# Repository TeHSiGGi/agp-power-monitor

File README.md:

# AGP Power Monitor

The APM is a monitoring tool to determine the exact power consumption of an AGP Graphics Card.
It measures both power provided by the AGP slot as well as through external power sources via: 

- 6 pin Mini-Fit Jr. from Molex (PCIe Power) 
- 4 Pin AMP Mate-n-Lok 1-480424-0 (mostly known as Molex connector, though it isn't one).

## Hardware

At the heart of APM is a custom AGP Riser card which consists mainly of an STM32F103C8T6 and three INA3221 power monitors. 

It measures the voltages and currents of the AGP slot as well as of external power providers. Additionally there are two alternative inputs which can be used to measure any user-chosen external power rail as long as it is within specification.

### Power Rails

The following power rails are being measured by the APM.

| Interface | Rail |
| -- | -- |
| AGP slot | 12V |
| AGP slot | 5V |
| AGP slot | 3.3V |
| AGP slot | VDDQ |
| External power | 12V (6Pin) |
| External power | 12V (4Pin) |
| External power | 5V (4Pin) |
| Alternative input | A |
| Alternative input | B |

### Resolution and limits

Each rail can measure:

- Up to 26V of voltage at 8mV steps
- Up to 10A of current at 4mA steps

These resolution values have to be take with a grain of salt, since these are theoretical numbers. The 26V and 10A are the absolute maximum ratings and must not be exceeded at any time.

### Connections:

- 2 keyed AGP gold finger connector
- Universal AGP slot
- Mini-Fit Jr 6 Pin input and output
- Mate-n-Lok 4 Pin input and output
- 2 Screw terminals for alternative channels A and B
- 4 Pin header for additional I2C devices
- 4 Pin header for STlink programming
- USB Mini B interface for connecting to a PC running the monitoring software

## Firmware

The APM uses an STM32F103C8T6 as its main processor. It serves as a USB interface providing fast access to the data provided by the INA3221.

The firmware is built using Platform.io and programmed via the 4 pin header on the board using STlink.

## Software

The monitoring software for APM is written in python and provides the following capabilities:

- Real time monitoring of all power rails (voltage, current, power)
- Automated calculation of minimum, maximum and average values over time of measurement
- Automated calculation of overall power per interface (AGP slot, external power and alternative inputs)
- Automated calculation of total power of all interfaces combined

## Known issues

- The layout of the AGP gold-fingers is a bit offset in the second and third segment
- CRC checking in the python application not implemented

## Wishlist for the future

- Plotting

## Reference values

To see some values from measured graphics cards, see [reference values](https://tehsiggi.github.io/agp-power-monitor/)

## Disclaimer

This project is provided as is. There is no support or warranty on any parts of it (this includes hardware design, firmware and software). Use it at your own risk.

The author will not be accountable for any damage or harm inflicted.

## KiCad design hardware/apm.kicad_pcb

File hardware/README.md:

# AGP Power Monitor Hardware

## Project Overview

The AGP Power Monitor is uses a custom AGP riser card to measure and monitor power consumption of AGP cards. It provides real-time voltage and current measurements for the various power rails used by AGP graphics cards, allowing for detailed power analysis and troubleshooting.

## Hardware Design

### Main Components

- **AGP Connectors**: Edge connector for AGP cards and slot connector for motherboard interface
- **Power Measurement**: INA3221 triple-channel power monitors for measuring voltage and current
- **Microcontroller**: STM32F103C8T6 MCU for data processing and USB communication
- **Power Supply**: All logic is powered via the USB input
- **USB Interface**: USB connectivity for data output and device control

### Design Notes

The PCB is a multi-layer design featuring:
- 4 layer with dedicated ground and power planes
- length matches AGP data lines

The USB input is using a polyfuse to prevent damage in case of shortcuts. The 3.3V output of the onboard regulator must not be loaded with more than 250mA. 

You can use the I2C header to connect additional hardware if needed.

The board features pin headers on the backside that can be used for calibration and rail measurement with external measurement equipment.

### Key Features

1. **Inline Power Measurement**: Non-intrusive monitoring between motherboard and graphics card
2. **Multiple Rail Monitoring**: Simultaneous monitoring of AGP power rails (3.3V, 5V, 12V, VDDQ)
3. **External Power Input**: Additional power connectors for supplementary power testing
4. **I²C Expansion**: I²C interface for connecting additional sensors or displays
5. **USB Interface**: Data logging and real-time monitoring via USB

## Connectors and Interfaces

| Connector | Description | Function |
|-----------|-------------|----------|
| J201 | AGP Edge Connector | Connects to motherboard AGP slot |
| J202 | AGP Slot Connector | Receives AGP graphics card |
| J301/J302 | External Power | 6Pin External 12V power input connectors |
| J303/J304 | External Power | 4Pin 5V/12V power output connector |
| J305/J306 | Alternative Power | Alternative power measurement points |
| J501 | USB Connector | USB data interface |
| J502 | I²C Header | External I²C device connection |

## KiCad Files and Libraries

This project is designed using KiCad 9.0. The directory includes:

- `apm.kicad_pro` - KiCad project file
- `apm.kicad_sch` - Main schematic file
- `apm.kicad_pcb` - PCB layout file
- `lib/` - Custom component libraries:
  - AGP edge connector footprints and symbols
  - AGP slot connector footprints and symbols
  - Power connector footprints and symbols

### Schematic Organization

The schematic is organized into multiple sheets for clarity:

1. **Main Sheet**: Overall system connections
2. **AGP Connectors**: AGP interface connections
3. **External Power**: Power input and conditioning circuits
4. **Sensors**: Power measurement circuits using INA3221
5. **USB Interface**: STM32 microcontroller and USB interface

## Setup Instructions

### Assembly Notes

1. The board requires SMD soldering capabilities (down to 0603 components, QFN packages)
2. Pay special attention to the alignment of AGP connectors
3. The PCB is designed for standard 1.6mm thickness
4. Edge plating is required for the AGP edge connector
5. Beveling (20°) is used during manufacturing

The PCBs have successfully been manufactured at pcbway.com

## BOM

| Part Type | Value/Model | Footprint | Qty | Comment |
|-----------|-------------|-----------|-----|---------|
| Capacitors | 4µ7 | 1206 | 2 | Bulk capacitors for 12V rail |
| | 22µ | 1206 | 12 | Bulk capacitors for 3.3V, 5V and VDDQ rail, USB Bus power |
| | 1µ | 0603 | 10 | Bypass capacitors for external and alternative inputs |
| | 100n | 0603 | 16 | Bypass capacitors and filter capacitors for INA3221|
| | 10µ | 1206 | 1 | Bypass capacitor for 3.3V from USB power |
| | 20p | 0603 | 4 | Crystal load capacitors |
| | 10n | 0603 | 1 | Capacitor for reset circuit |
| Resistors | 0R01 | 2816 | 9 | Current shunt resistors |
| | 10 | 0603 | 18 | Pull-up/pull-down resistors |
| | 22 | 0603 | 2 | USB termination resistors |
| | 1M | 0603 | 1 | Crystal load resistor |
| | 10k | 0603 | 1 | Pull-up resistor |
| | 4k7 | 0603 | 1 | Pull-up resistor |
| | 3k3 | 0603 | 3 | Pull-up resistors |
| | 220 | 0603 | 3 | LED current limiting resistors |
| ICs | INA3221 | VQFN | 3 | Triple-channel power monitor |
| | MCP1703AT3302ECB | SOT-23 | 1 | 3.3V voltage regulator |
| | STM32F103C8T6 | LQFP-48 | 1 | 32-bit ARM microcontroller |
| Protection | PRTR5V0U2X | SOT-143 | 2 | USB ESD protection |
| | P4SMAJ5.0A | SMA | 1 | TVS diode |
| | 200mA | 1812 | 1 | Polyfuse |
| Connectors | AGP Edge Connector | edge_universal | 1 | Motherboard interface |
| | 145376-2 | 145376-2 AMP | 1 | AGP card slot |
| | 12V/3.3V/VDDQ/5V/GND PROBE | Pin Header 2 Pin 2.54mm | 10 | Test points |
| | 39301060 | Molex_Mini-Fit_Jr_5569-06A2_2x03_P4.20mm_Horizontal | 2 | 6-pin power connectors |
| | 641737-1 | 641737-1 | 2 | 4-pin power connectors |
| | Screw_Terminal_01x02 | 5.08mm Horizontal | 2 | Alternative power input |
| | USB_B_Mini | Wuerth 65100516121 | 1 | USB interface |
| | I2C/STLink Headers | PinHeader 4 Pin 2.54mm | 2 | Expansion/Programming headers |
| Indicators | LED | 1206 | 3 | Status indicators |
| Crystals | 8MHz | HC49l | 1 | Main MCU oscillator |
| | 32.768kHz | DS10 | 1 | RTC oscillator |

## Revision History

- Rev 1.0.0: Initial hardware design

## Disclaimer

This project is provided as is. There is no support or warranty on any parts of it (this includes hardware design, firmware and software). Use it at your own risk.

The author will not be accountable for any damage or harm inflicted.

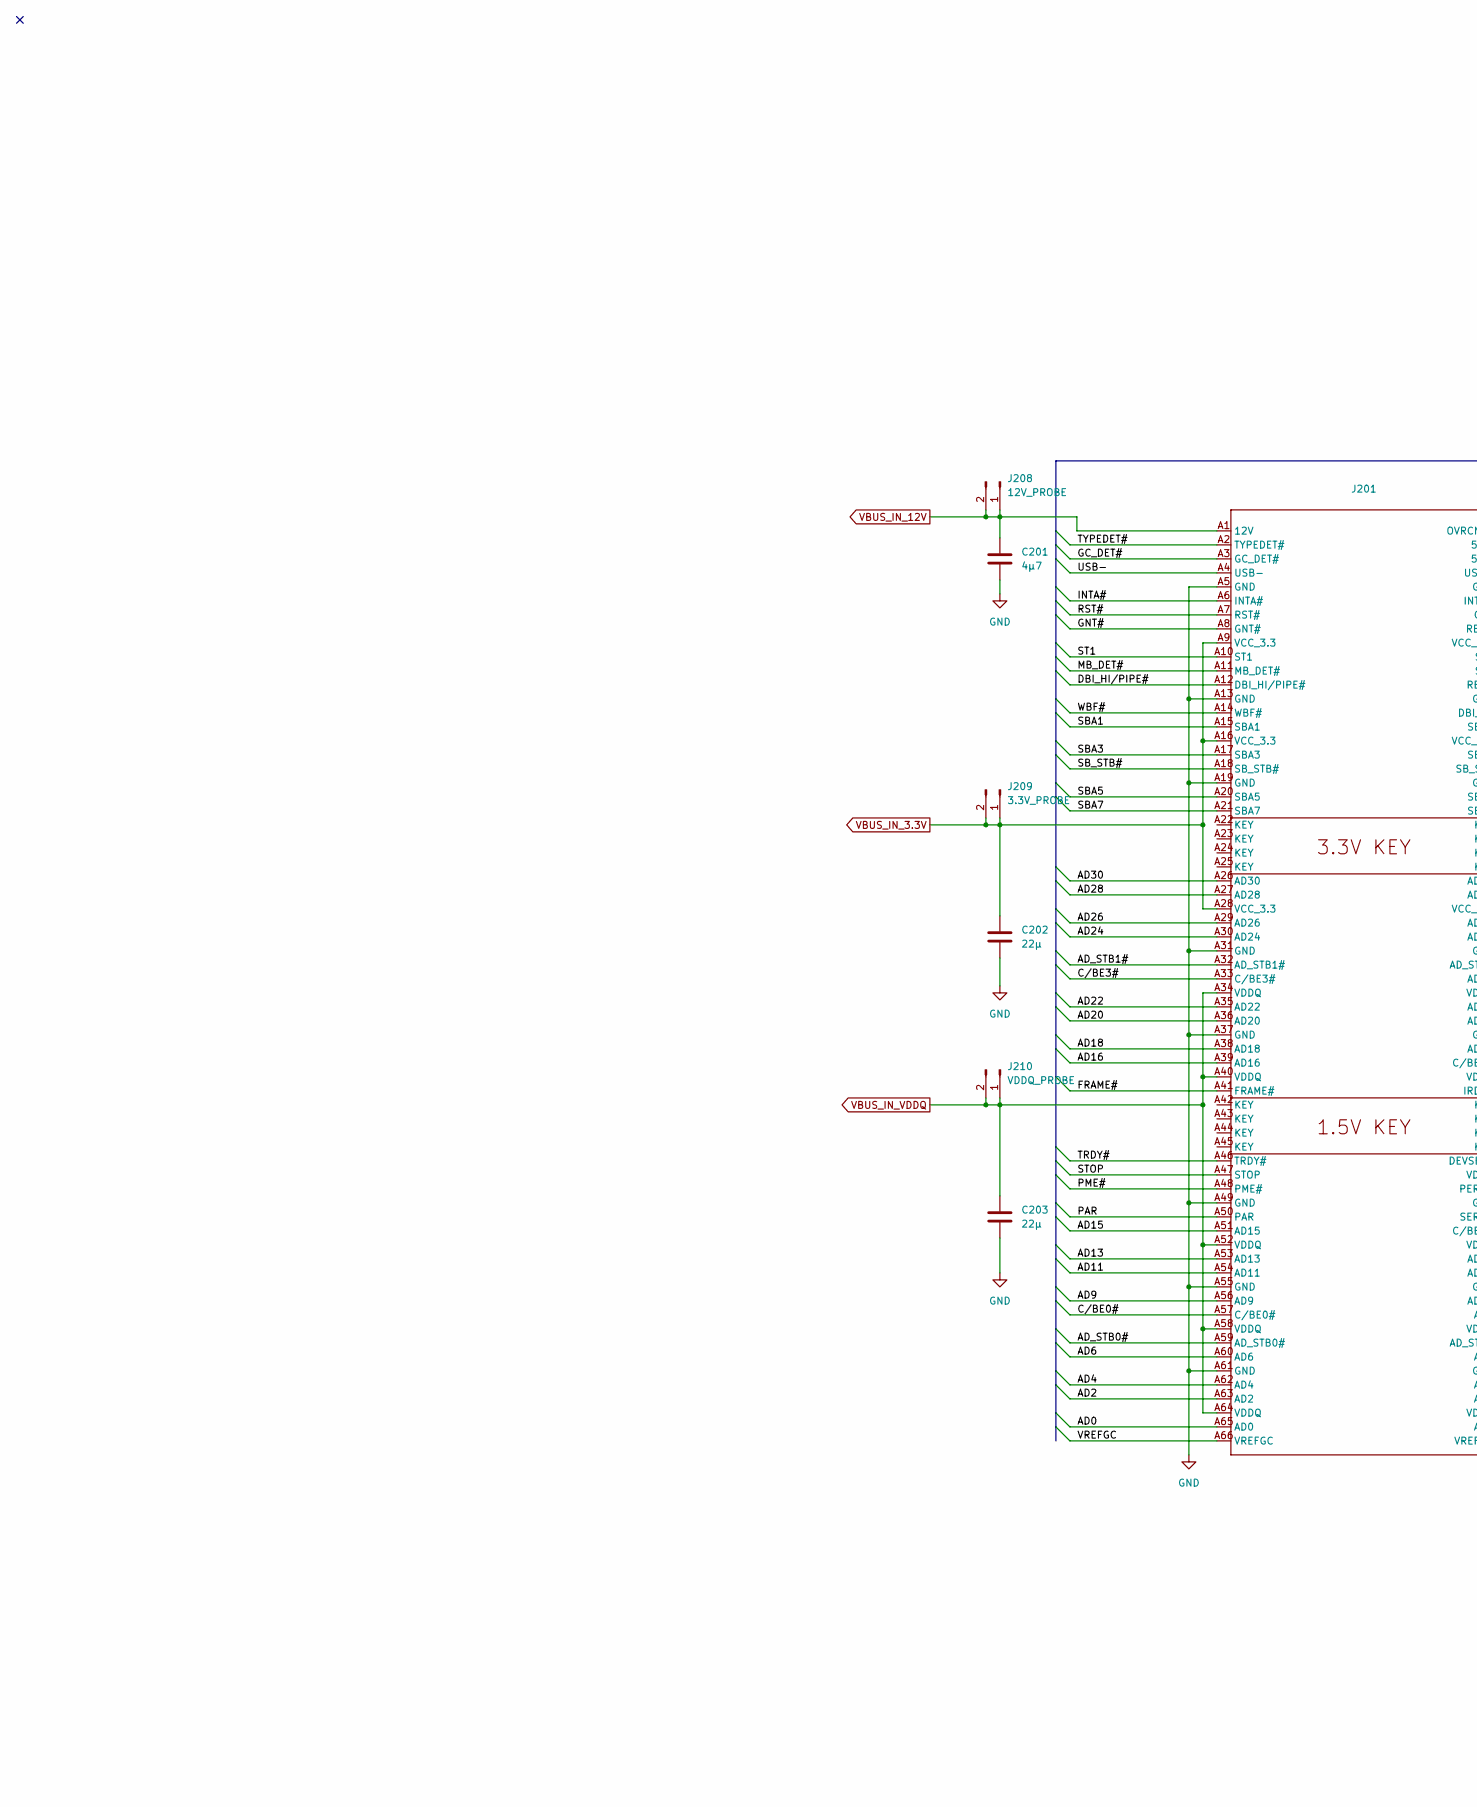
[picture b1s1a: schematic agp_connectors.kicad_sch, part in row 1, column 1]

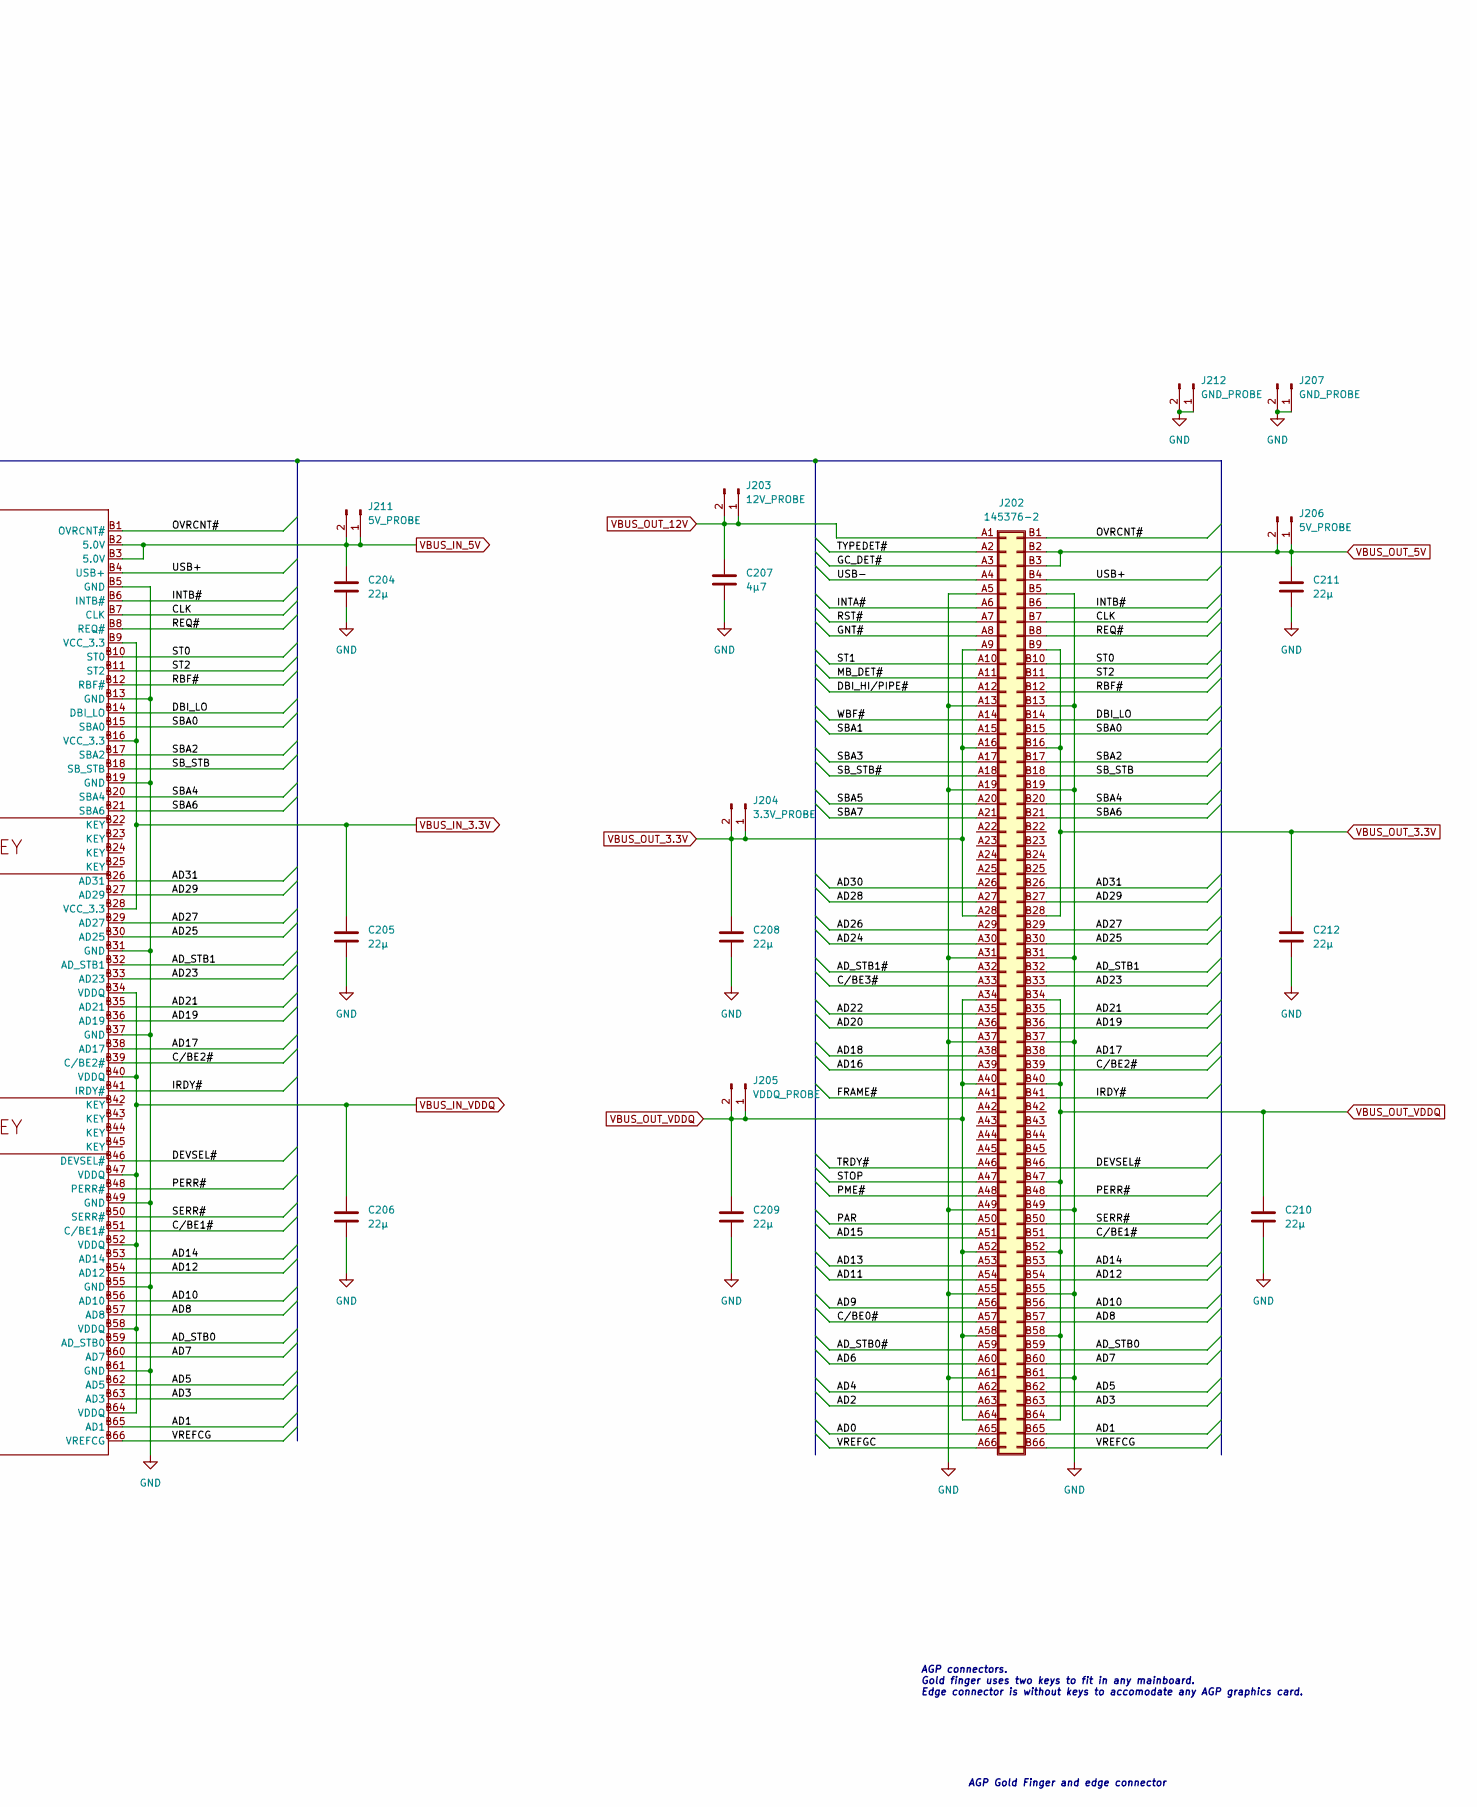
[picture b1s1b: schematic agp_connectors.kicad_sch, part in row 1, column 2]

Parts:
C201, C207: 4µ7; C_1206_3216Metric
C202, C203, C204, C205, C206, C208, C209, C210, C211, C212: 22µ; C_1206_3216Metric
J201: edge_universal
J202: 145376-2; Conn_AMP_1MM_STD_EDGE_132_POS_145376-2
J203, J208: 12V_PROBE; PinHeader_1x02_P2.54mm_Vertical
J204, J209: 3.3V_PROBE; PinHeader_1x02_P2.54mm_Vertical
J205, J210: VDDQ_PROBE; PinHeader_1x02_P2.54mm_Vertical
J206, J211: 5V_PROBE; PinHeader_1x02_P2.54mm_Vertical
J207, J212: GND_PROBE; PinHeader_1x02_P2.54mm_Vertical

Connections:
/agp_connectors/AD0: J201.A65 (AD0), J202.A65 (65)
/agp_connectors/AD1: J201.B65 (AD1), J202.B65 (131)
/agp_connectors/AD2: J201.A63 (AD2), J202.A63 (63)
/agp_connectors/AD3: J201.B63 (AD3), J202.B63 (129)
/agp_connectors/AD4: J201.A62 (AD4), J202.A62 (62)
/agp_connectors/AD5: J201.B62 (AD5), J202.B62 (128)
/agp_connectors/AD6: J201.A60 (AD6), J202.A60 (60)
/agp_connectors/AD7: J201.B60 (AD7), J202.B60 (126)
/agp_connectors/AD8: J201.B57 (AD8), J202.B57 (123)
/agp_connectors/AD9: J201.A56 (AD9), J202.A56 (56)
/agp_connectors/AD10: J201.B56 (AD10), J202.B56 (122)
/agp_connectors/AD11: J201.A54 (AD11), J202.A54 (54)
/agp_connectors/AD12: J201.B54 (AD12), J202.B54 (120)
/agp_connectors/AD13: J201.A53 (AD13), J202.A53 (53)
/agp_connectors/AD14: J201.B53 (AD14), J202.B53 (119)
/agp_connectors/AD15: J201.A51 (AD15), J202.A51 (51)
/agp_connectors/AD16: J201.A39 (AD16), J202.A39 (39)
/agp_connectors/AD17: J201.B38 (AD17), J202.B38 (104)
/agp_connectors/AD18: J201.A38 (AD18), J202.A38 (38)
/agp_connectors/AD19: J201.B36 (AD19), J202.B36 (102)
/agp_connectors/AD20: J201.A36 (AD20), J202.A36 (36)
/agp_connectors/AD21: J201.B35 (AD21), J202.B35 (101)
/agp_connectors/AD22: J201.A35 (AD22), J202.A35 (35)
/agp_connectors/AD23: J201.B33 (AD23), J202.B33 (99)
/agp_connectors/AD24: J201.A30 (AD24), J202.A30 (30)
/agp_connectors/AD25: J201.B30 (AD25), J202.B30 (96)
/agp_connectors/AD26: J201.A29 (AD26), J202.A29 (29)
/agp_connectors/AD27: J201.B29 (AD27), J202.B29 (95)
/agp_connectors/AD28: J201.A27 (AD28), J202.A27 (27)
/agp_connectors/AD29: J201.B27 (AD29), J202.B27 (93)
/agp_connectors/AD30: J201.A26 (AD30), J202.A26 (26)
/agp_connectors/AD31: J201.B26 (AD31), J202.B26 (92)
/agp_connectors/AD_STB0: J201.B59 (AD_STB0), J202.B59 (125)
/agp_connectors/AD_STB0#: J201.A59 (AD_STB0#), J202.A59 (59)
/agp_connectors/AD_STB1: J201.B32 (AD_STB1), J202.B32 (98)
/agp_connectors/AD_STB1#: J201.A32 (AD_STB1#), J202.A32 (32)
/agp_connectors/CLK: J201.B7 (CLK), J202.B7 (73)
/agp_connectors/C/BE0#: J201.A57 (C/BE0#), J202.A57 (57)
/agp_connectors/C/BE1#: J201.B51 (C/BE1#), J202.B51 (117)
/agp_connectors/C/BE2#: J201.B39 (C/BE2#), J202.B39 (105)
/agp_connectors/C/BE3#: J201.A33 (C/BE3#), J202.A33 (33)
/agp_connectors/DBI_HI/PIPE#: J201.A12 (DBI_HI/PIPE#), J202.A12 (12)
/agp_connectors/DBI_LO: J201.B14 (DBI_LO), J202.B14 (80)
/agp_connectors/DEVSEL#: J201.B46 (DEVSEL#), J202.B46 (112)
/agp_connectors/FRAME#: J201.A41 (FRAME#), J202.A41 (41)
/agp_connectors/GC_DET#: J201.A3 (GC_DET#), J202.A3 (3)
/agp_connectors/GNT#: J201.A8 (GNT#), J202.A8 (8)
/agp_connectors/INTA#: J201.A6 (INTA#), J202.A6 (6)
/agp_connectors/INTB#: J201.B6 (INTB#), J202.B6 (72)
/agp_connectors/IRDY#: J201.B41 (IRDY#), J202.B41 (107)
/agp_connectors/MB_DET#: J201.A11 (MB_DET#), J202.A11 (11)
/agp_connectors/OVRCNT#: J201.B1 (OVRCNT#), J202.B1 (67)
/agp_connectors/PAR: J201.A50 (PAR), J202.A50 (50)
/agp_connectors/PERR#: J201.B48 (PERR#), J202.B48 (114)
/agp_connectors/PME#: J201.A48 (PME#), J202.A48 (48)
/agp_connectors/RBF#: J201.B12 (RBF#), J202.B12 (78)
/agp_connectors/REQ#: J201.B8 (REQ#), J202.B8 (74)
/agp_connectors/RST#: J201.A7 (RST#), J202.A7 (7)
/agp_connectors/SBA0: J201.B15 (SBA0), J202.B15 (81)
/agp_connectors/SBA1: J201.A15 (SBA1), J202.A15 (15)
/agp_connectors/SBA2: J201.B17 (SBA2), J202.B17 (83)
/agp_connectors/SBA3: J201.A17 (SBA3), J202.A17 (17)
/agp_connectors/SBA4: J201.B20 (SBA4), J202.B20 (86)
/agp_connectors/SBA5: J201.A20 (SBA5), J202.A20 (20)
/agp_connectors/SBA6: J201.B21 (SBA6), J202.B21 (87)
/agp_connectors/SBA7: J201.A21 (SBA7), J202.A21 (21)
/agp_connectors/SB_STB: J201.B18 (SB_STB), J202.B18 (84)
/agp_connectors/SB_STB#: J201.A18 (SB_STB#), J202.A18 (18)
/agp_connectors/SERR#: J201.B50 (SERR#), J202.B50 (116)
/agp_connectors/ST0: J201.B10 (ST0), J202.B10 (76)
/agp_connectors/ST1: J201.A10 (ST1), J202.A10 (10)
/agp_connectors/ST2: J201.B11 (ST2), J202.B11 (77)
/agp_connectors/STOP: J201.A47 (STOP), J202.A47 (47)
/agp_connectors/TRDY#: J201.A46 (TRDY#), J202.A46 (46)
/agp_connectors/TYPEDET#: J201.A2 (TYPEDET#), J202.A2 (2)
/agp_connectors/USB+: J201.B4 (USB+), J202.B4 (70)
/agp_connectors/USB-: J201.A4 (USB-), J202.A4 (4)
/agp_connectors/VREFCG: J201.B66 (VREFCG), J202.B66 (132)
/agp_connectors/VREFGC: J201.A66 (VREFGC), J202.A66 (66)
/agp_connectors/WBF#: J201.A14 (WBF#), J202.A14 (14)
GND: C201.2, C202.2, C203.2, C204.2, C205.2, C206.2, C207.2, C208.2, C209.2, C210.2, C211.2, C212.2, J201.A5 (GND), J201.A13 (GND), J201.A19 (GND), J201.A31 (GND), J201.A37 (GND), J201.A49 (GND), J201.A55 (GND), J201.A61 (GND), J201.B5 (GND), J201.B13 (GND), J201.B19 (GND), J201.B31 (GND), J201.B37 (GND), J201.B49 (GND), J201.B55 (GND), J201.B61 (GND), J202.A5 (5), J202.A13 (13), J202.A19 (19), J202.A31 (31), J202.A37 (37), J202.A49 (49), J202.A55 (55), J202.A61 (61), J202.B5 (71), J202.B13 (79), J202.B19 (85), J202.B31 (97), J202.B37 (103), J202.B49 (115), J202.B55 (121), J202.B61 (127), J207.1, J207.2, J212.1, J212.2; also elsewhere on the board
VBUS_IN_3.3V: C202.1, C205.1, J201.A9 (VCC_3.3), J201.A16 (VCC_3.3), J201.A28 (VCC_3.3), J201.B9 (VCC_3.3), J201.B16 (VCC_3.3), J201.B28 (VCC_3.3), J209.1, J209.2; also elsewhere on the board
VBUS_IN_5V: C204.1, J201.B2 (5.0V), J201.B3 (5.0V), J211.1, J211.2; also elsewhere on the board
VBUS_IN_12V: C201.1, J201.A1 (12V), J208.1, J208.2; also elsewhere on the board
VBUS_IN_VDDQ: C203.1, C206.1, J201.A34 (VDDQ), J201.A40 (VDDQ), J201.A52 (VDDQ), J201.A58 (VDDQ), J201.A64 (VDDQ), J201.B34 (VDDQ), J201.B40 (VDDQ), J201.B47 (VDDQ), J201.B52 (VDDQ), J201.B58 (VDDQ), J201.B64 (VDDQ), J210.1, J210.2; also elsewhere on the board
VBUS_OUT_3.3V: C208.1, C212.1, J202.A9 (9), J202.A16 (16), J202.A28 (28), J202.B9 (75), J202.B16 (82), J202.B28 (94), J204.1, J204.2; also elsewhere on the board
VBUS_OUT_5V: C211.1, J202.B2 (68), J202.B3 (69), J206.1, J206.2; also elsewhere on the board
VBUS_OUT_12V: C207.1, J202.A1 (1), J203.1, J203.2; also elsewhere on the board
VBUS_OUT_VDDQ: C209.1, C210.1, J202.A34 (34), J202.A40 (40), J202.A52 (52), J202.A58 (58), J202.A64 (64), J202.B34 (100), J202.B40 (106), J202.B47 (113), J202.B52 (118), J202.B58 (124), J202.B64 (130), J205.1, J205.2; also elsewhere on the board

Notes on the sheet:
AGP connectors. Gold finger uses two keys to fit in any mainboard. Edge connector is without keys to accomodate any AGP graphics card.
AGP Gold Finger and edge connector

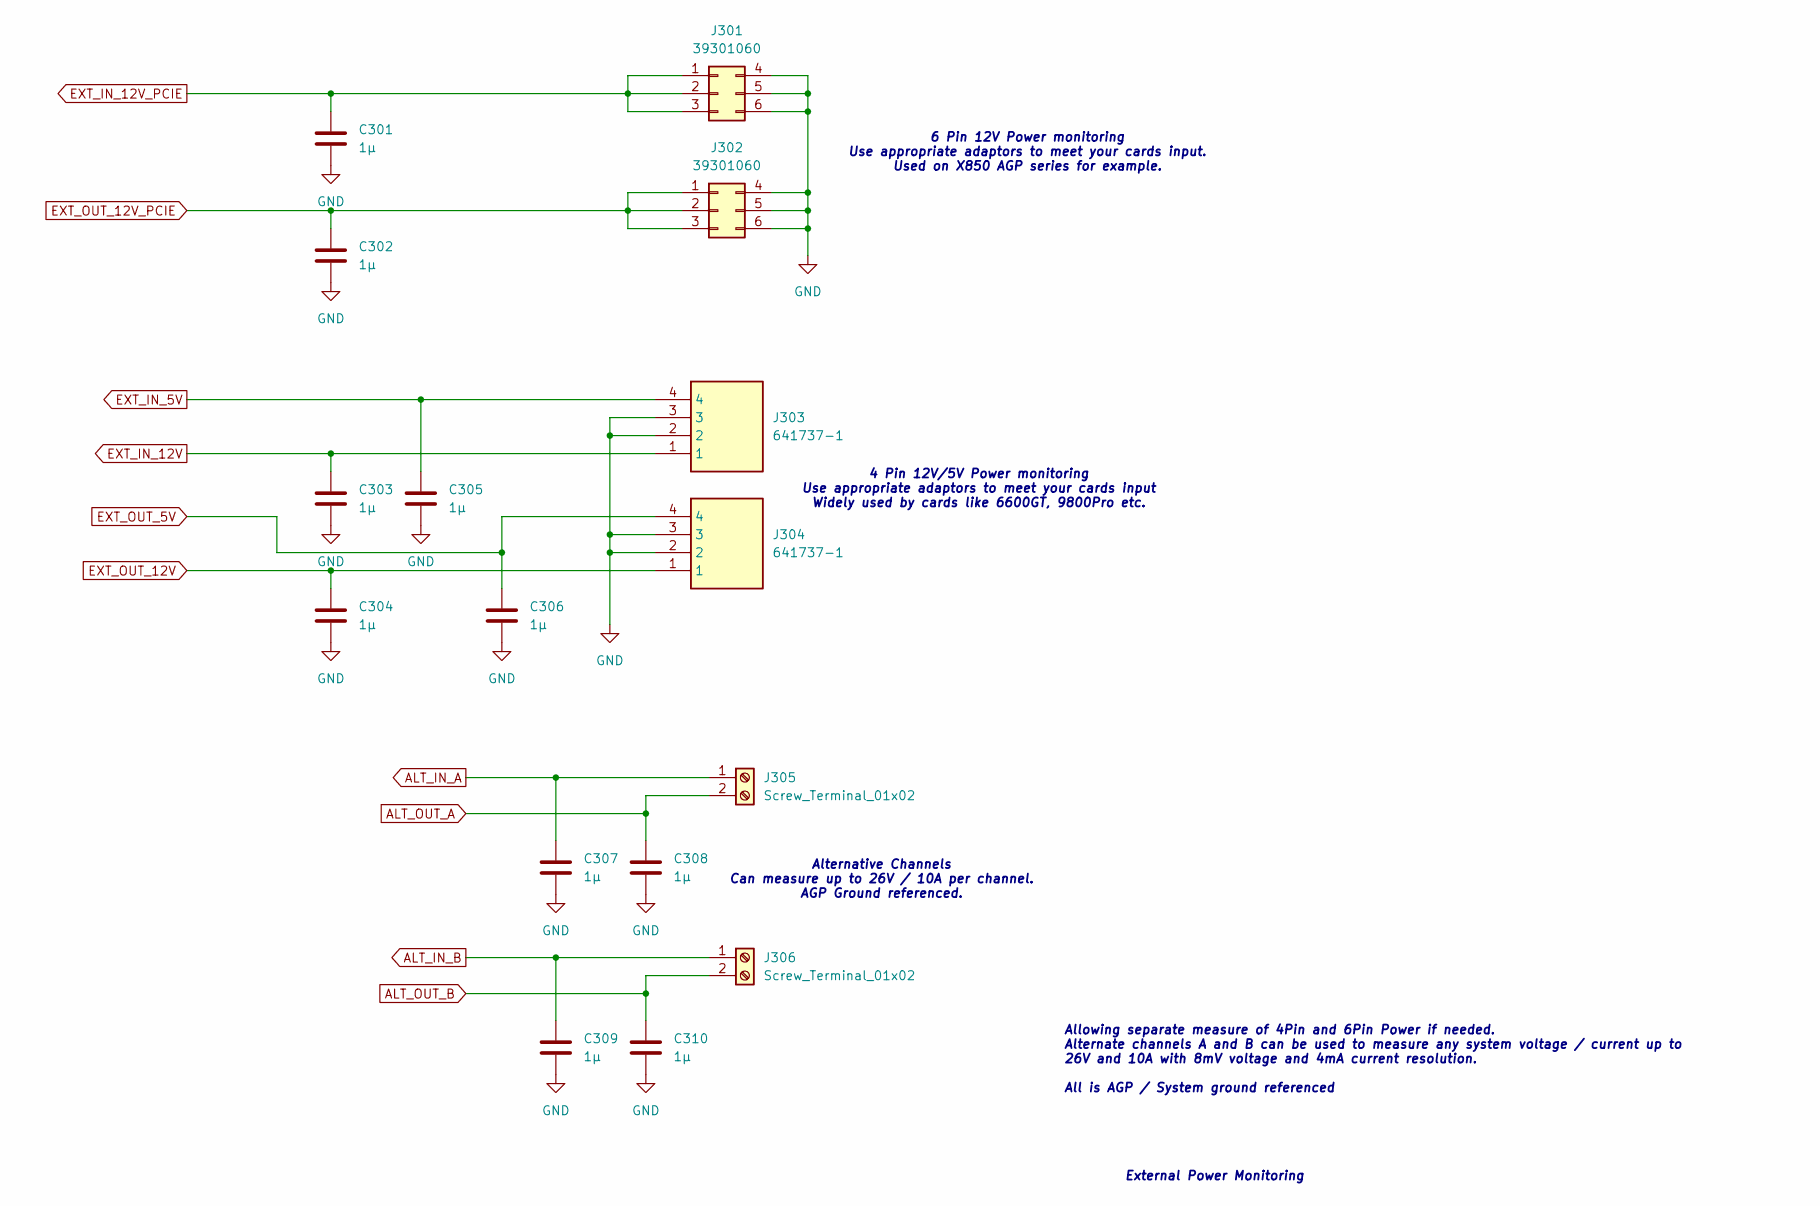
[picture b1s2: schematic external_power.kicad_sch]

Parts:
C301, C302, C303, C304, C305, C306, C307, C308, C309, C310: 1µ; C_0603_1608Metric
J301, J302: 39301060; Molex_Mini-Fit_Jr_5569-06A2_2x03_P4.20mm_Horizontal
J303, J304: 641737-1; Mouser Part Number 571-6417371
J305, J306: Screw_Terminal_01x02; TerminalBlock_RND_205-00232_1x02_P5.08mm_Horizontal

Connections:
ALT_IN_A: C307.1, J305.1; also elsewhere on the board
ALT_IN_B: C309.1, J306.1; also elsewhere on the board
ALT_OUT_A: C308.1, J305.2; also elsewhere on the board
ALT_OUT_B: C310.1, J306.2; also elsewhere on the board
EXT_IN_5V: C305.1, J303.4; also elsewhere on the board
EXT_IN_12V: C303.1, J303.1; also elsewhere on the board
EXT_IN_12V_PCIE: C301.1, J301.1, J301.2, J301.3; also elsewhere on the board
EXT_OUT_5V: C306.1, J304.4; also elsewhere on the board
EXT_OUT_12V: C304.1, J304.1; also elsewhere on the board
EXT_OUT_12V_PCIE: C302.1, J302.1, J302.2, J302.3; also elsewhere on the board
GND: C301.2, C302.2, C303.2, C304.2, C305.2, C306.2, C307.2, C308.2, C309.2, C310.2, J301.4, J301.5, J301.6, J302.4, J302.5, J302.6, J303.2, J303.3, J304.2, J304.3; also elsewhere on the board

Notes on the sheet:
Allowing separate measure of 4Pin and 6Pin Power if needed. Alternate channels A and B can be used to measure any system voltage / current up to 26V and 10A with 8mV voltage and 4mA current resolution. All is AGP / System ground referenced
Alternative Channels Can measure up to 26V / 10A per channel. AGP Ground referenced.
6 Pin 12V Power monitoring Use appropriate adaptors to meet your cards input. Used on X850 AGP series for example.
External Power Monitoring
4 Pin 12V/5V Power monitoring Use appropriate adaptors to meet your cards input Widely used by cards like 6600GT, 9800Pro etc.

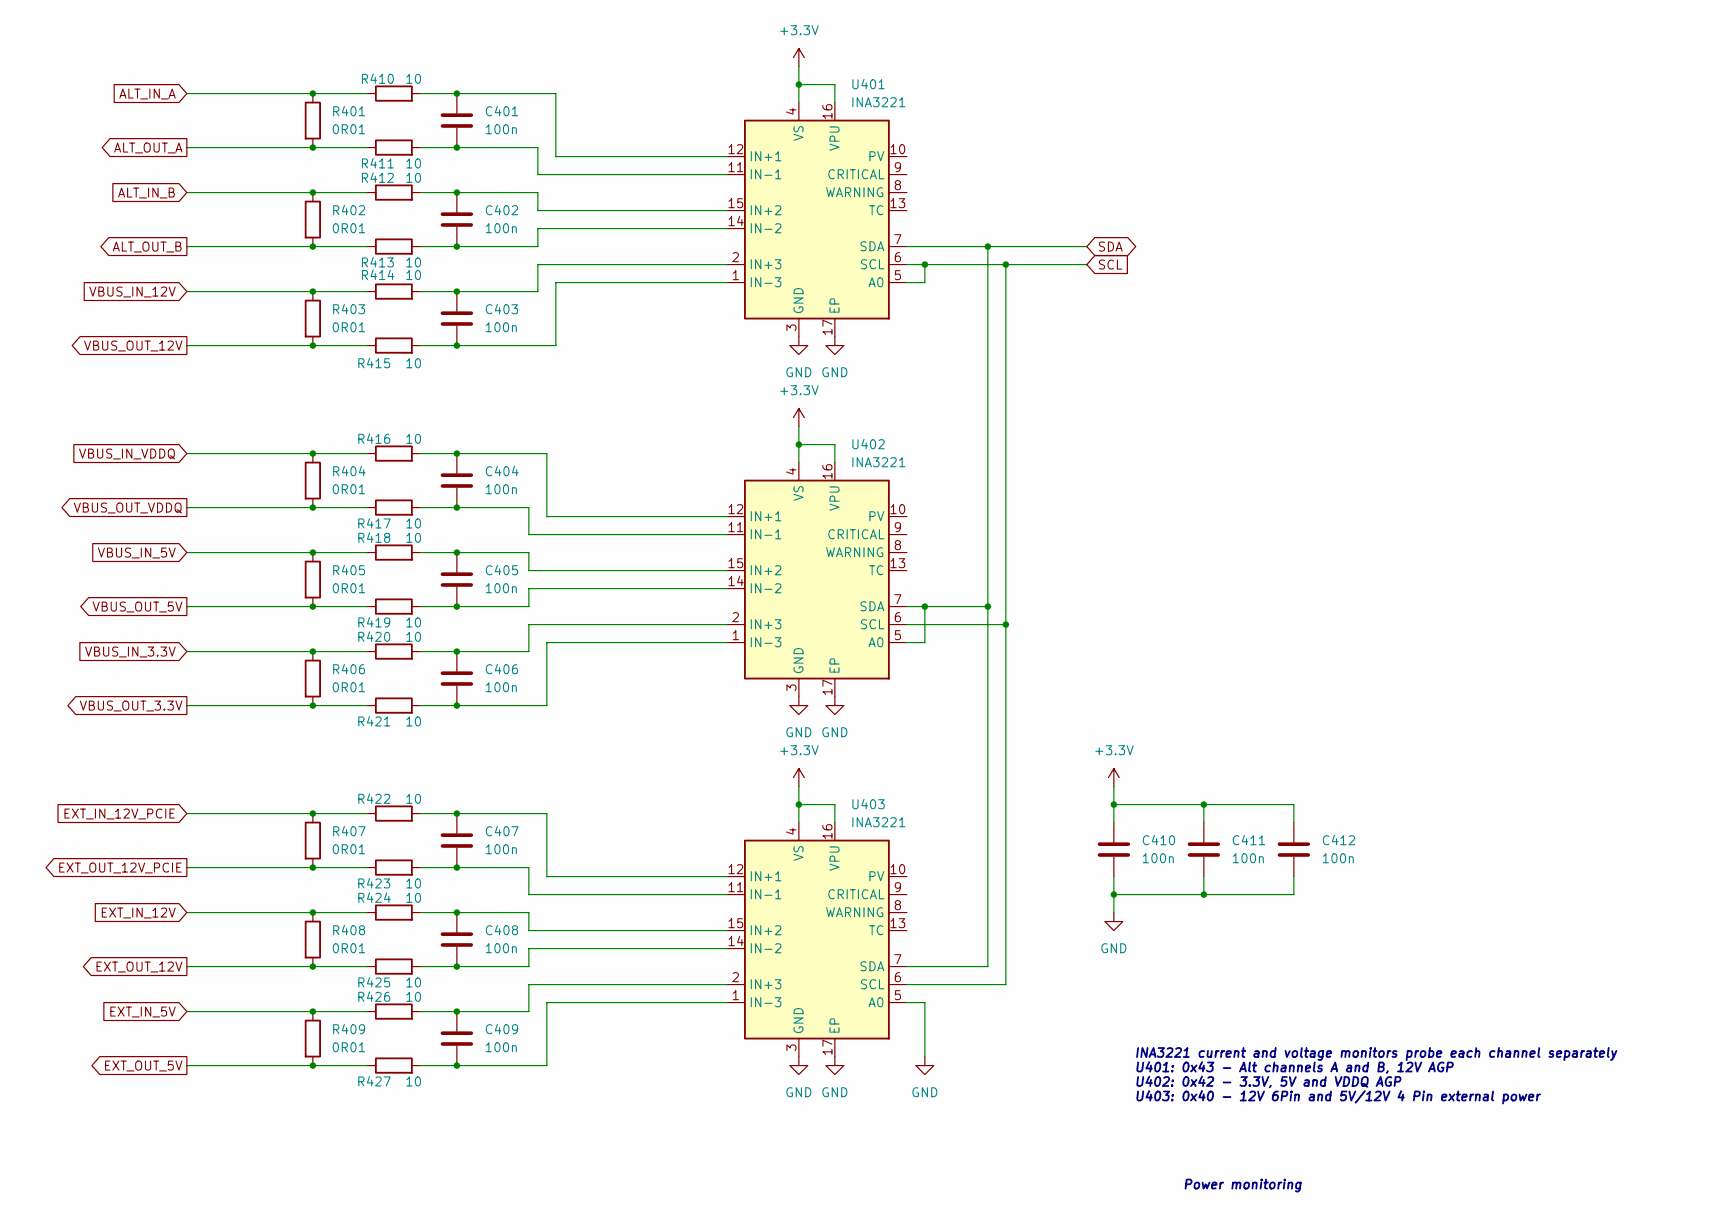
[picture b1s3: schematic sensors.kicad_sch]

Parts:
C401, C402, C403, C404, C405, C406, C407, C408, C409, C410, C411, C412: 100n; C_0603_1608Metric
R401, R402, R403, R404, R405, R406, R407, R408, R409: 0R01; R_2816_7142Metric
R410, R411, R412, R413, R414, R415, R416, R417, R418, R419, R420, R421, R422, R423, R424, R425, R426, R427: 10; R_0603_1608Metric
U401, U402, U403: INA3221; Texas_RGV0016A_VQFN-16-1EP_4x4mm_P0.65mm_EP2.1x2.1mm

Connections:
+3.3V: C410.1, C411.1, C412.1, U401.4 (VS), U401.16 (VPU), U402.4 (VS), U402.16 (VPU), U403.4 (VS), U403.16 (VPU); also elsewhere on the board
ALT_IN_A: R401.1, R410.1; also elsewhere on the board
ALT_IN_B: R402.1, R412.1; also elsewhere on the board
ALT_OUT_A: R401.2, R411.1; also elsewhere on the board
ALT_OUT_B: R402.2, R413.1; also elsewhere on the board
EXT_IN_5V: R409.1, R426.1; also elsewhere on the board
EXT_IN_12V: R408.1, R424.1; also elsewhere on the board
EXT_IN_12V_PCIE: R407.1, R422.1; also elsewhere on the board
EXT_OUT_5V: R409.2, R427.1; also elsewhere on the board
EXT_OUT_12V: R408.2, R425.1; also elsewhere on the board
EXT_OUT_12V_PCIE: R407.2, R423.1; also elsewhere on the board
GND: C410.2, C411.2, C412.2, U401.3 (GND), U401.17 (EP), U402.3 (GND), U402.17 (EP), U403.3 (GND), U403.5 (A0), U403.17 (EP); also elsewhere on the board
unnamed: C401.1, R410.2, U401.12 (IN+1)
unnamed: C402.1, R412.2, U401.15 (IN+2)
unnamed: C403.1, R414.2, U401.2 (IN+3)
unnamed: C401.2, R411.2, U401.11 (IN-1)
unnamed: C402.2, R413.2, U401.14 (IN-2)
unnamed: C403.2, R415.2, U401.1 (IN-3)
unnamed: C404.1, R416.2, U402.12 (IN+1)
unnamed: C405.1, R418.2, U402.15 (IN+2)
unnamed: C406.1, R420.2, U402.2 (IN+3)
unnamed: C404.2, R417.2, U402.11 (IN-1)
unnamed: C405.2, R419.2, U402.14 (IN-2)
unnamed: C406.2, R421.2, U402.1 (IN-3)
unnamed: C407.1, R422.2, U403.12 (IN+1)
unnamed: C408.1, R424.2, U403.15 (IN+2)
unnamed: C409.1, R426.2, U403.2 (IN+3)
unnamed: C407.2, R423.2, U403.11 (IN-1)
unnamed: C408.2, R425.2, U403.14 (IN-2)
unnamed: C409.2, R427.2, U403.1 (IN-3)
SCL: U401.5 (A0), U401.6 (SCL), U402.6 (SCL), U403.6 (SCL); also elsewhere on the board
SDA: U401.7 (SDA), U402.5 (A0), U402.7 (SDA), U403.7 (SDA); also elsewhere on the board
VBUS_IN_3.3V: R406.1, R420.1; also elsewhere on the board
VBUS_IN_5V: R405.1, R418.1; also elsewhere on the board
VBUS_IN_12V: R403.1, R414.1; also elsewhere on the board
VBUS_IN_VDDQ: R404.1, R416.1; also elsewhere on the board
VBUS_OUT_3.3V: R406.2, R421.1; also elsewhere on the board
VBUS_OUT_5V: R405.2, R419.1; also elsewhere on the board
VBUS_OUT_12V: R403.2, R415.1; also elsewhere on the board
VBUS_OUT_VDDQ: R404.2, R417.1; also elsewhere on the board

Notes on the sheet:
INA3221 current and voltage monitors probe each channel separately U401: 0x43 - Alt channels A and B, 12V AGP U402: 0x42 - 3.3V, 5V and VDDQ AGP U403: 0x40 - 12V 6Pin and 5V/12V 4 Pin external power
Power monitoring

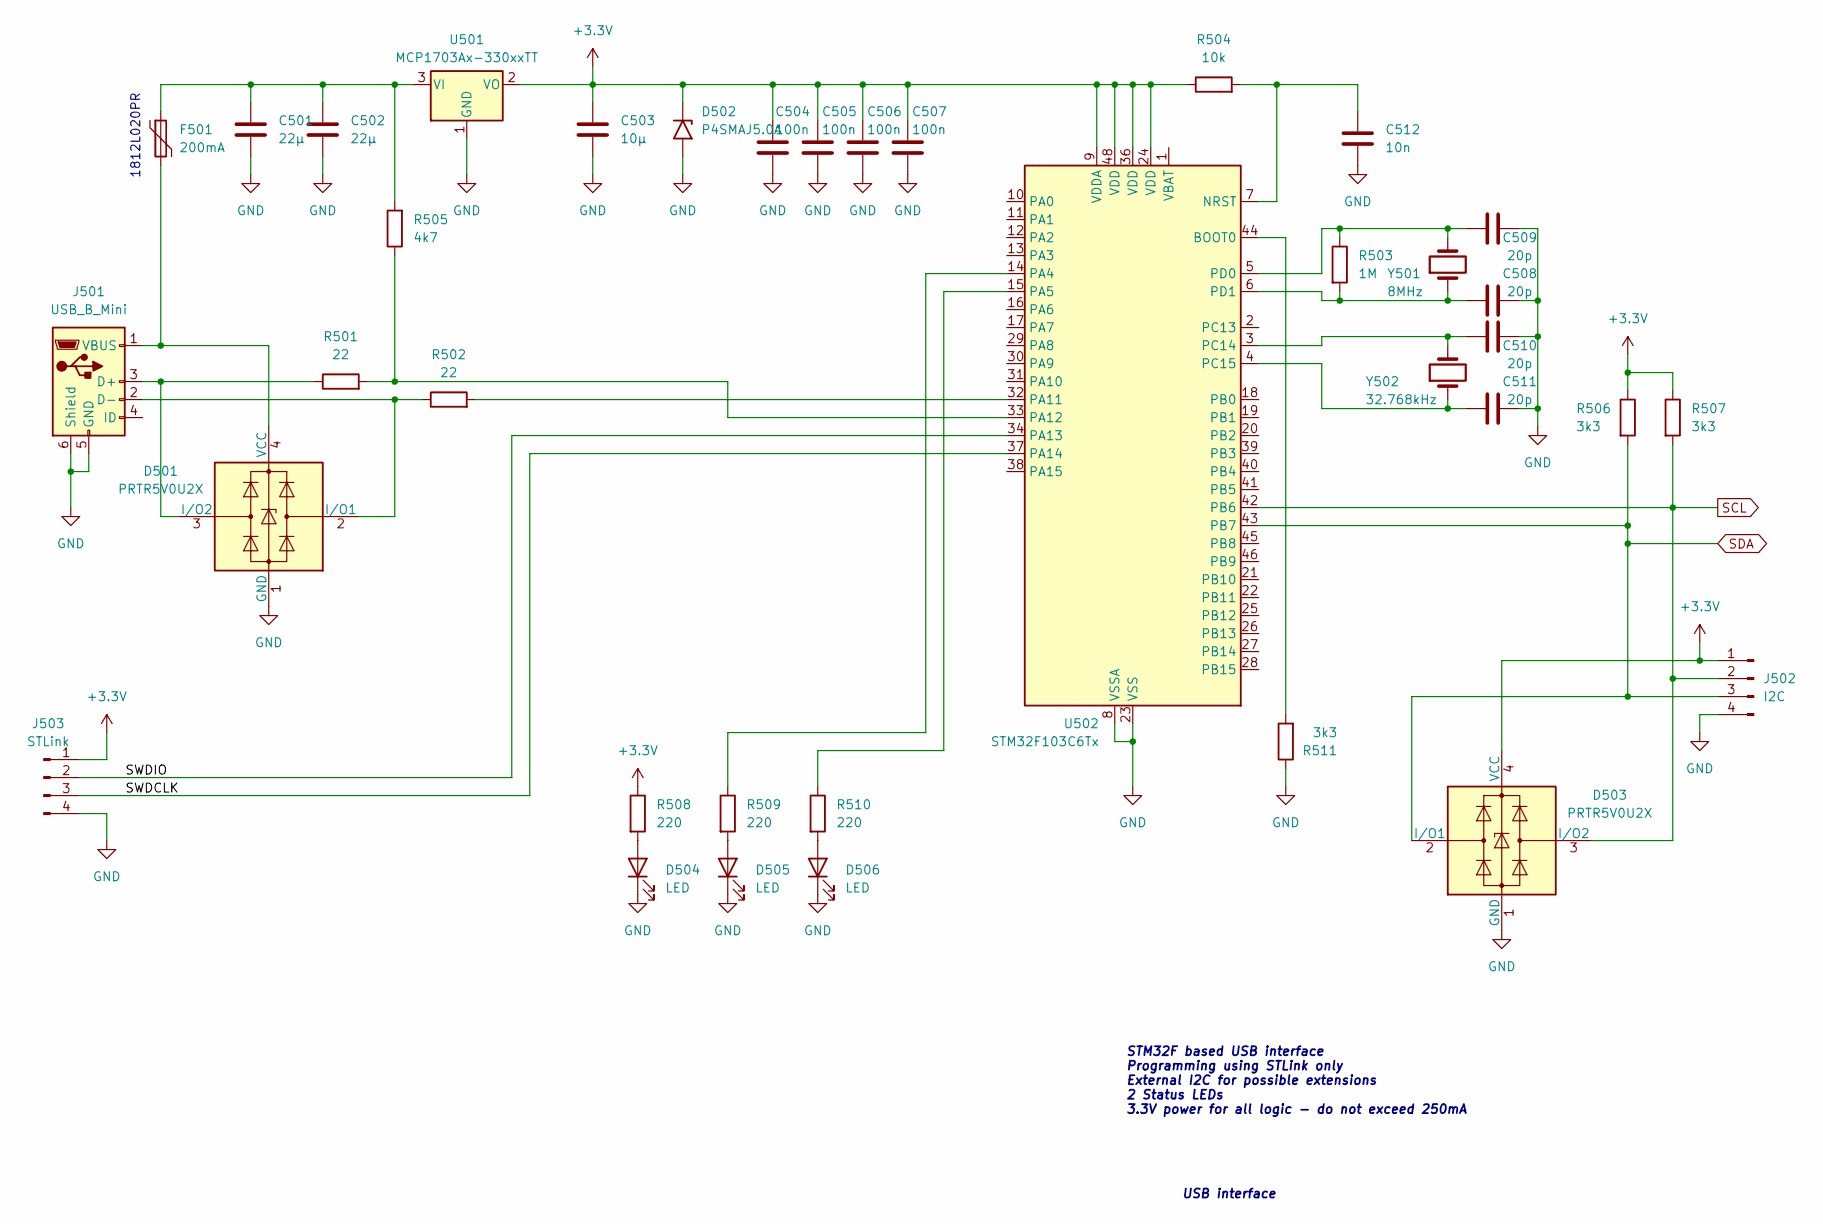
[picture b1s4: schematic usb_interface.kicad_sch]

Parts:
C501, C502: 22µ; C_1206_3216Metric
C503: 10µ; C_1206_3216Metric
C504, C505, C506, C507: 100n; C_0603_1608Metric
C508, C509, C510, C511: 20p; C_0603_1608Metric
C512: 10n; C_0603_1608Metric
D501, D503: PRTR5V0U2X; SOT-143
D502: P4SMAJ5.0A; D_SMA
D504, D505, D506: LED; LED_1206_3216Metric
F501: 200mA; Fuse_1812_4532Metric
J501: USB_B_Mini; USB_Mini-B_Wuerth_65100516121_Horizontal
J502: I2C; PinHeader_1x04_P2.54mm_Vertical
J503: STLink; PinHeader_1x04_P2.54mm_Vertical
R501, R502: 22; R_0603_1608Metric
R503: 1M; R_0603_1608Metric
R504: 10k; R_0603_1608Metric
R505: 4k7; R_0603_1608Metric
R506, R507, R511: 3k3; R_0603_1608Metric
R508, R509, R510: 220; R_0603_1608Metric
U501: MCP1703Ax-330xxTT; SOT-23
U502: STM32F103C6Tx; LQFP-48_7x7mm_P0.5mm
Y501: 8MHz; Crystal_HC49-U_Vertical
Y502: 32.768kHz; Crystal_DS10_D1.0mm_L4.3mm_Horizontal

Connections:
+3.3V: C503.1, C504.1, C505.1, C506.1, C507.1, D502.1 (A1), D503.4 (VCC), J502.1, J503.1, R504.1, R506.1, R507.1, R508.1, U501.2 (VO), U502.9 (VDDA), U502.24 (VDD), U502.36 (VDD), U502.48 (VDD); also elsewhere on the board
/usb_interface/SWDCLK: J503.3, U502.37 (PA14)
/usb_interface/SWDIO: J503.2, U502.34 (PA13)
GND: C501.2, C502.2, C503.2, C504.2, C505.2, C506.2, C507.2, C508.2, C509.2, C510.2, C511.2, C512.2, D501.1 (GND), D502.2 (A2), D503.1 (GND), D504.1 (K), D505.1 (K), D506.1 (K), J501.5 (GND), J501.6 (Shield), J502.4, J503.4, R511.1, U501.1 (GND), U502.8 (VSSA), U502.23 (VSS), U502.35 (VSS), U502.47 (VSS); also elsewhere on the board
unnamed: D501.2 (I/O1), J501.2 (D-), R502.1
unnamed: D501.3 (I/O2), J501.3 (D+), R501.1
unnamed: D501.4 (VCC), F501.2, J501.1 (VBUS)
unnamed: D504.2 (A), R508.2
unnamed: D505.2 (A), R509.2
unnamed: D506.2 (A), R510.2
unnamed: C501.1, C502.1, F501.1, R505.2, U501.3 (VI)
unnamed: R511.2, U502.44 (BOOT0)
unnamed: C512.1, R504.2, U502.7 (NRST)
unnamed: R509.1, U502.14 (PA4)
unnamed: R510.1, U502.15 (PA5)
unnamed: R502.2, U502.32 (PA11)
unnamed: R501.2, R505.1, U502.33 (PA12)
unnamed: C510.1, U502.3 (PC14), Y502.2
unnamed: C511.1, U502.4 (PC15), Y502.1
unnamed: C509.1, R503.1, U502.5 (PD0), Y501.2
unnamed: C508.1, R503.2, U502.6 (PD1), Y501.1
SCL: D503.3 (I/O2), J502.2, R507.2, U502.42 (PB6); also elsewhere on the board
SDA: D503.2 (I/O1), J502.3, R506.2, U502.43 (PB7); also elsewhere on the board

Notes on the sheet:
USB interface
STM32F based USB interface Programming using STLink only External I2C for possible extensions 2 Status LEDs 3.3V power for all logic - do not exceed 250mA
1812L020PR
